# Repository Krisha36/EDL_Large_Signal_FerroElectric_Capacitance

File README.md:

# EDL_Large_Signal_FerroElectric_Capacitance

### Link to our Notion Page
### https://www.notion.so/EDL-MON-03-2ea75040919c4b7b8f81075fa2af05f8
#### The repository contains all the PCB schematic and routing files, the code files for the ADC, DAC, UART implementation, and the CAD files.

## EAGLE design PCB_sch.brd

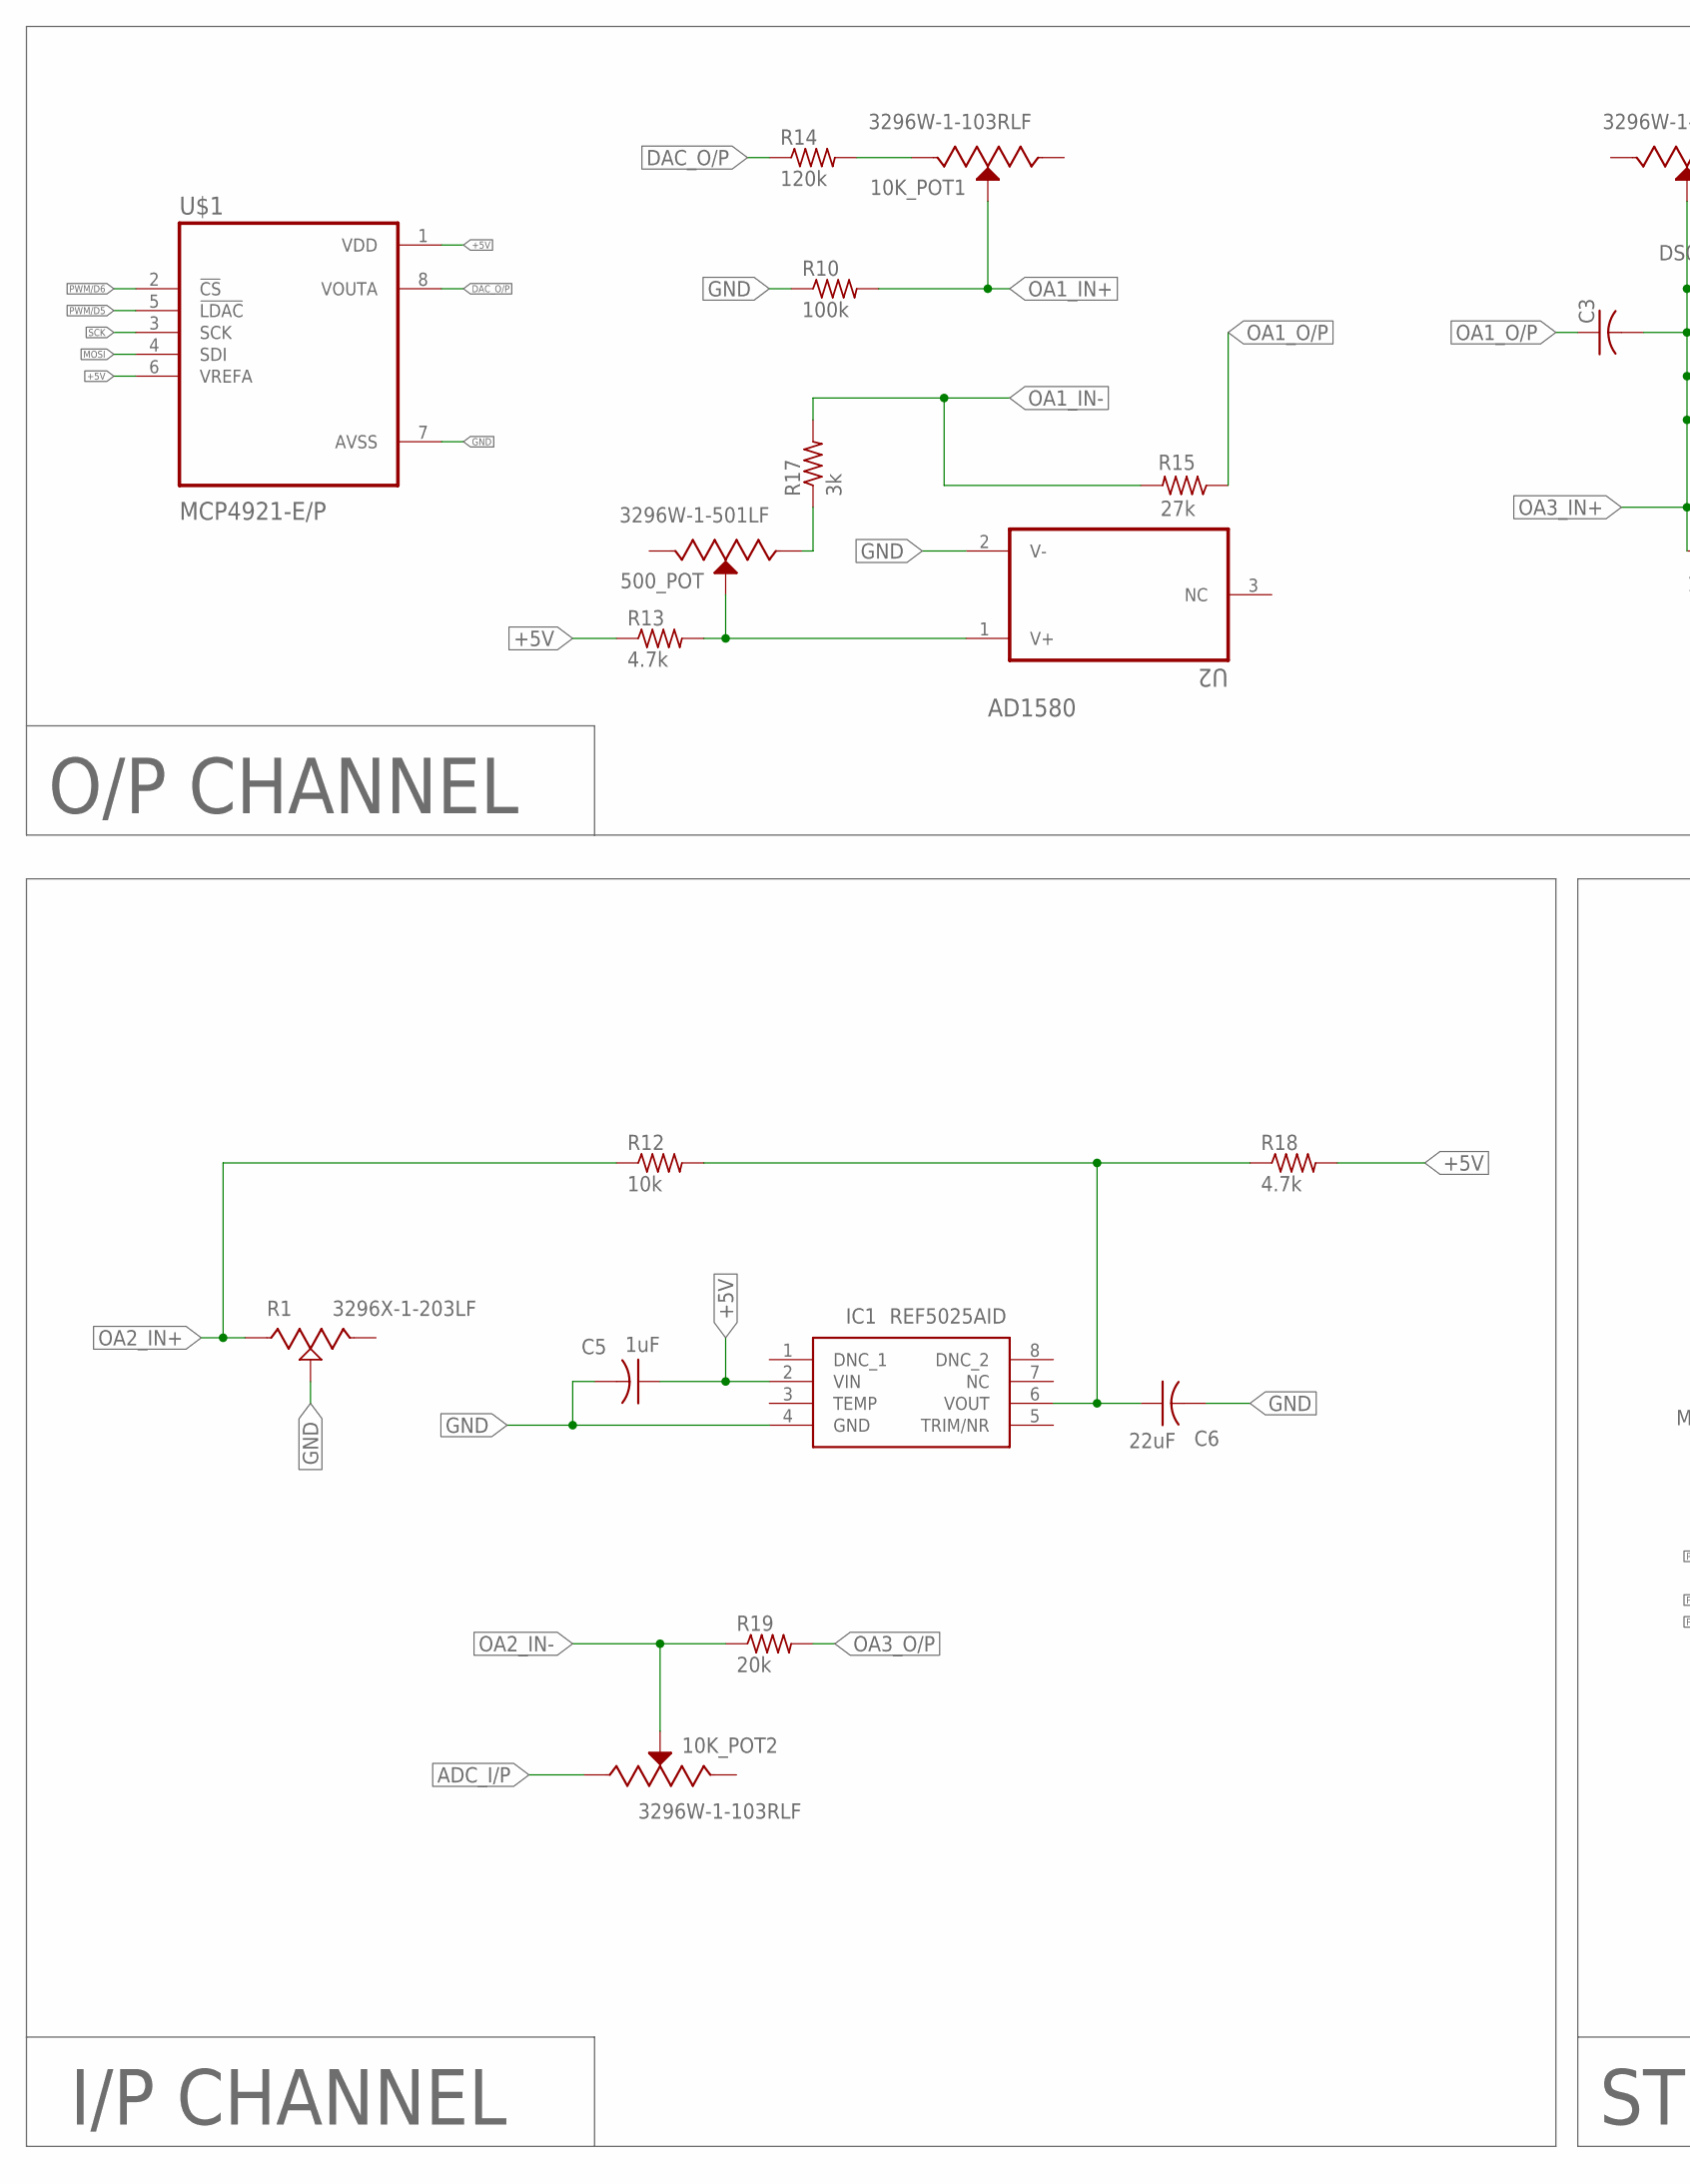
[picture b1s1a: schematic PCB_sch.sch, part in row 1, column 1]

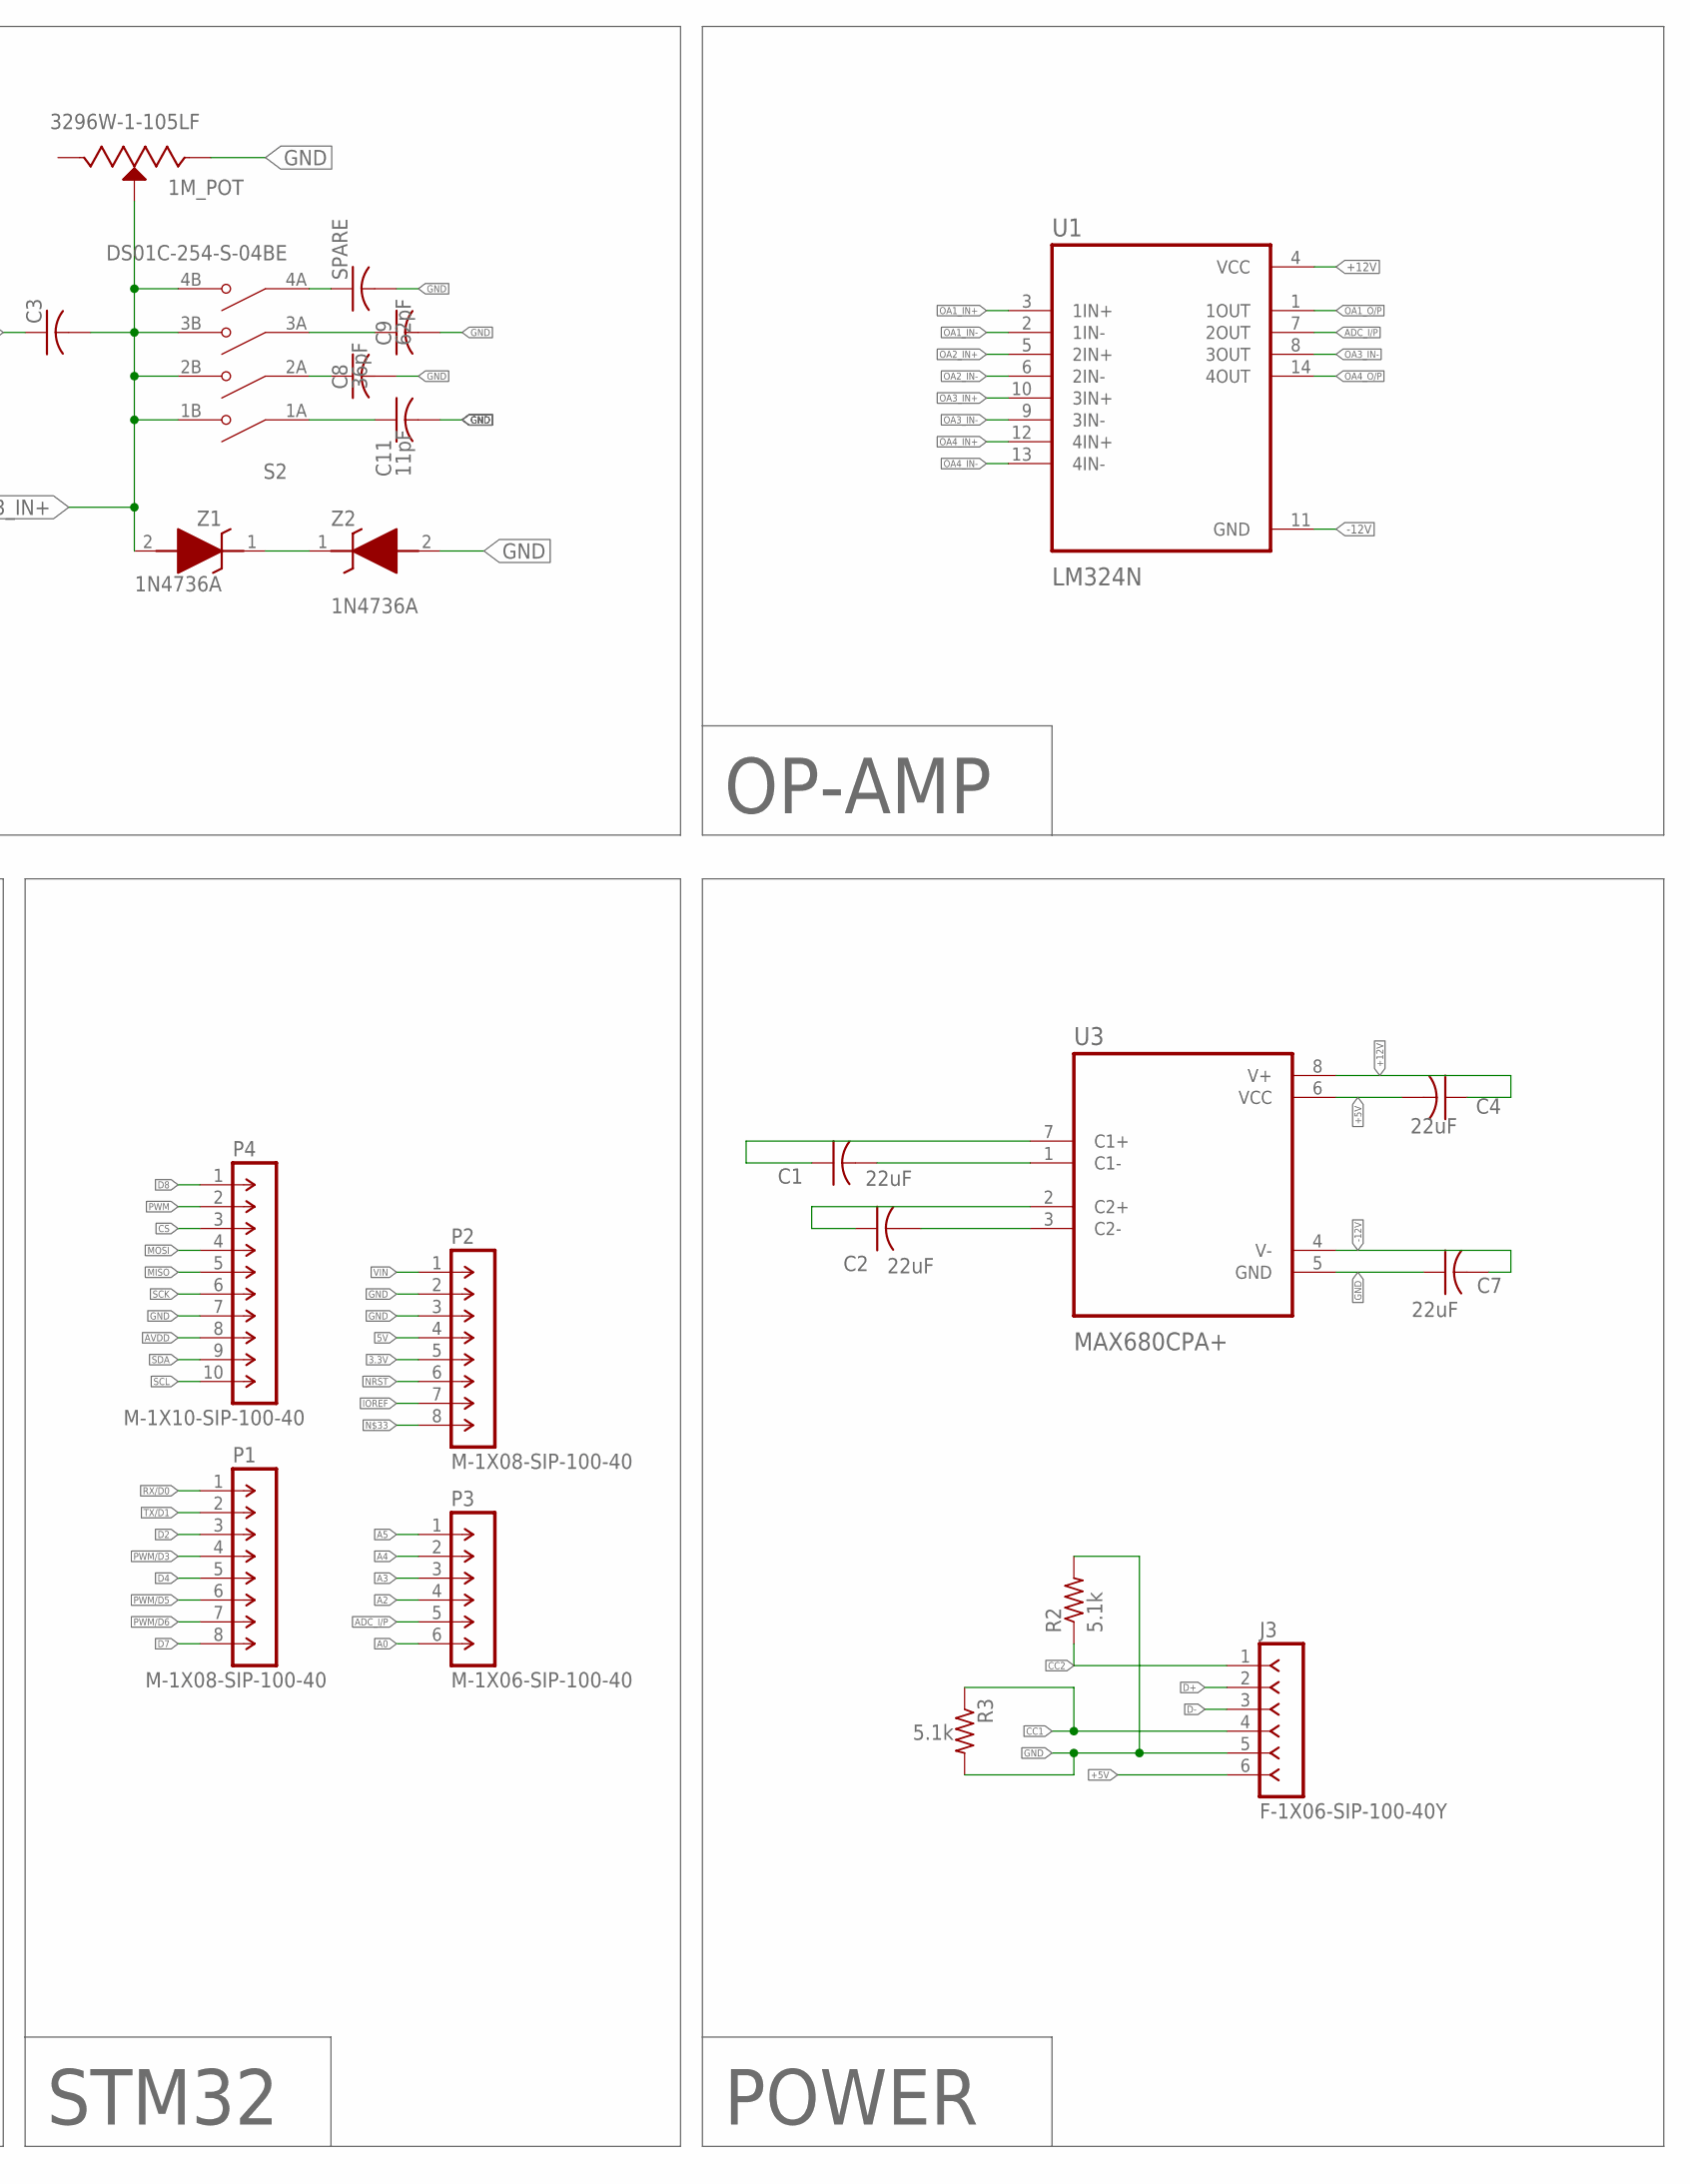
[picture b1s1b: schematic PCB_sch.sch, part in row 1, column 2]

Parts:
1M_POT: 3296W-1-105LF; TRIM_3296W-1-105LF
10K_POT1, 10K_POT2: 3296W-1-103RLF; TRIM_3296W-1-103RLF
500_POT: 3296W-1-501LF; TRIM_3296W-1-501LF
C1, C2, C4, C7: 22uF; C0805
C3: C-US050-030X075; C050-030X075
C5: 1uF; C0805K
C6: 22uF; C0805K
C8: 36pF; C0805
C9: 62pF; C0805
C11: 11pF; C0805
IC1: REF5025AID; SOIC127P600X175-8N
J3: F-1X06-SIP-100-40Y; SIP-100-06-40Y
P1, P2: M-1X08-SIP-100-40; SIP-100-08-40
P3: M-1X06-SIP-100-40; SIP-100-06-40
P4: M-1X10-SIP-100-40; SIP-100-10-40
R1: 3296X-1-203LF; TRIM_3296X-1-203LF
R2, R3: 5.1k; R0805
R10: 100k; M0805
R12: 10k; M0805
R13, R18: 4.7k; M0805
R14: 120k; M0805
R15: 27k; M0805
R17: 3k; M0805
R19: 20k; M0805
S2: DS01C-254-S-04BE; SW_DS01C-254-S-04BE
SPARE: C-USC0805; C0805
U1: LM324N; DIP794W45P254L1969H508Q14
U2: AD1580; SOT96P237X112-3N
U3: MAX680CPA+; DIP794W47P254L991H457Q8
U$1: MCP4921-E/P; DIP787W46P254L927H533Q8
Z1, Z2: 1N4736A; DIOAD1413W86L463D238

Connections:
3.3V: P2.5
5V: P2.4
+5V: C4.2, C5.1, IC1.2 (VIN), J3.6, R13.1, R18.2, U3.6 (VCC), U$1.1 (VDD), U$1.6 (VREFA)
+12V: C4.1, U1.4 (VCC), U3.8 (V+)
-12V: C7.2, U1.11 (GND), U3.4 (V-)
A0: P3.6
A2: P3.4
A3: P3.3
A4: P3.2
A5: P3.1
ADC_I/P: 10K_POT2.1 (CCW), P3.5, U1.7 (2OUT)
AVDD: P4.8
CC1: J3.4, R3.1
CC2: J3.1, R2.1
CS: P4.3
D2: P1.3
D4: P1.5
D7: P1.8
D8: P4.1
D+: J3.2
D-: J3.3
DAC_O/P: R14.1, U$1.8 (VOUTA)
GND: 1M_POT.1 (CCW), C5.2, C6.2, C7.1, C8.2, C9.2, C11.2, IC1.4 (GND), J3.5, P2.2, P2.3, P4.7, R1.2 (WIPER), R2.2, R3.2, R10.1, SPARE.2, U2.2 (V-), U3.5 (GND), U$1.7 (AVSS), Z2.2 (A)
IOREF: P2.7
MISO: P4.5
MOSI: P4.4, U$1.4 (SDI)
unnamed: 10K_POT1.3 (CW), R14.2
unnamed: 10K_POT1.2 (WIPER), R10.2
unnamed: R15.2, R17.2
unnamed: 500_POT.1 (CCW), R17.1
unnamed: C1.2, U3.1 (C1-)
unnamed: 500_POT.2 (WIPER), R13.2, U2.1 (V+)
unnamed: C6.1, IC1.6 (VOUT), R12.2, R18.1
unnamed: Z1.1 (K), Z2.1 (K)
unnamed: C1.1, U3.7 (C1+)
unnamed: C2.2, U3.3 (C2-)
unnamed: C2.1, U3.2 (C2+)
unnamed: C9.1, S2.3A (COM3)
unnamed: S2.4A (COM4), SPARE.1
unnamed: C11.1, S2.1A (COM1)
unnamed: C8.1, S2.2A (COM2)
NRST: P2.6
OA1_IN+: U1.3 (1IN+)
OA1_IN-: U1.2 (1IN-)
OA1_O/P: C3.1, R15.1, U1.1 (1OUT)
OA2_IN+: R1.1 (CCW), R12.1, U1.5 (2IN+)
OA2_IN-: 10K_POT2.2 (WIPER), R19.1, U1.6 (2IN-)
OA3_IN+: 1M_POT.2 (WIPER), C3.2, S2.1B (NO1), S2.2B (NO2), S2.3B (NO3), S2.4B (NO4), U1.10 (3IN+), Z1.2 (A)
OA3_IN-: U1.8 (3OUT), U1.9 (3IN-)
OA3_O/P: R19.2
OA4_IN+: U1.12 (4IN+)
OA4_IN-: U1.13 (4IN-)
OA4_O/P: U1.14 (4OUT)
PWM: P4.2
PWM/D3: P1.4
PWM/D5: P1.6, U$1.5 (!LDAC)
PWM/D6: P1.7, U$1.2 (!CS)
RX/D0: P1.1
SCK: P4.6, U$1.3 (SCK)
SCL: P4.10
SDA: P4.9
TX/D1: P1.2
VIN: P2.1

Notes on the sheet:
POWER
STM32
I/P CHANNEL
OP-AMP
O/P CHANNEL

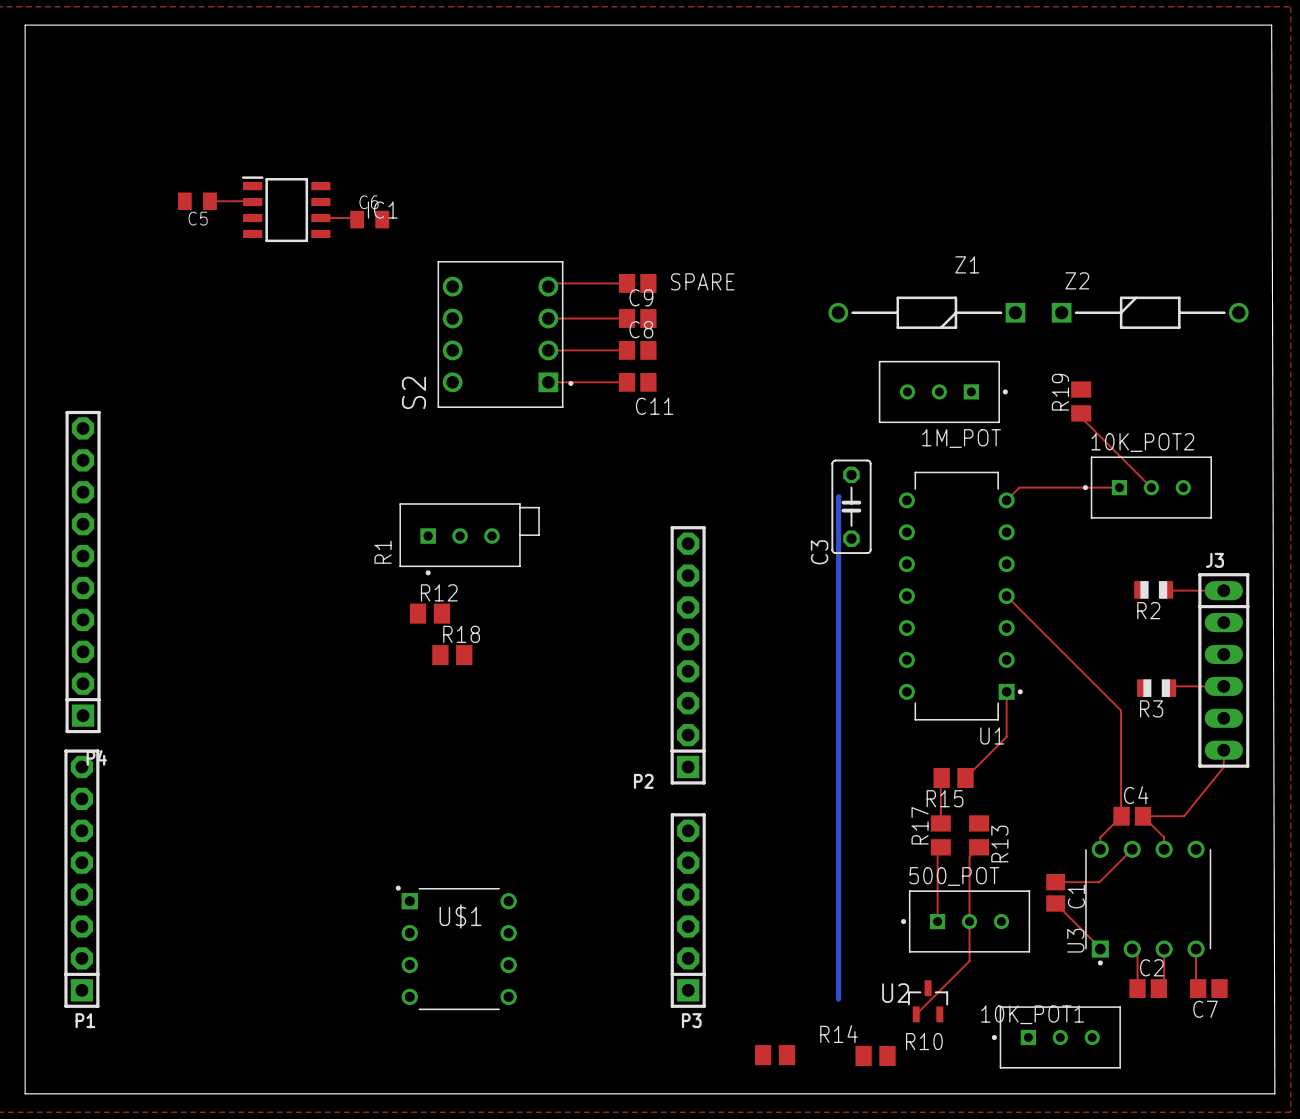
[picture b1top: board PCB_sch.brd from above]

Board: 2 copper layers, 99.5 x 85.1 mm, 39 parts (0 on the bottom side), 32 nets.

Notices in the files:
parts and their libraries:
con-headers-jp: Copyright (C) 2008, Bob Starr
